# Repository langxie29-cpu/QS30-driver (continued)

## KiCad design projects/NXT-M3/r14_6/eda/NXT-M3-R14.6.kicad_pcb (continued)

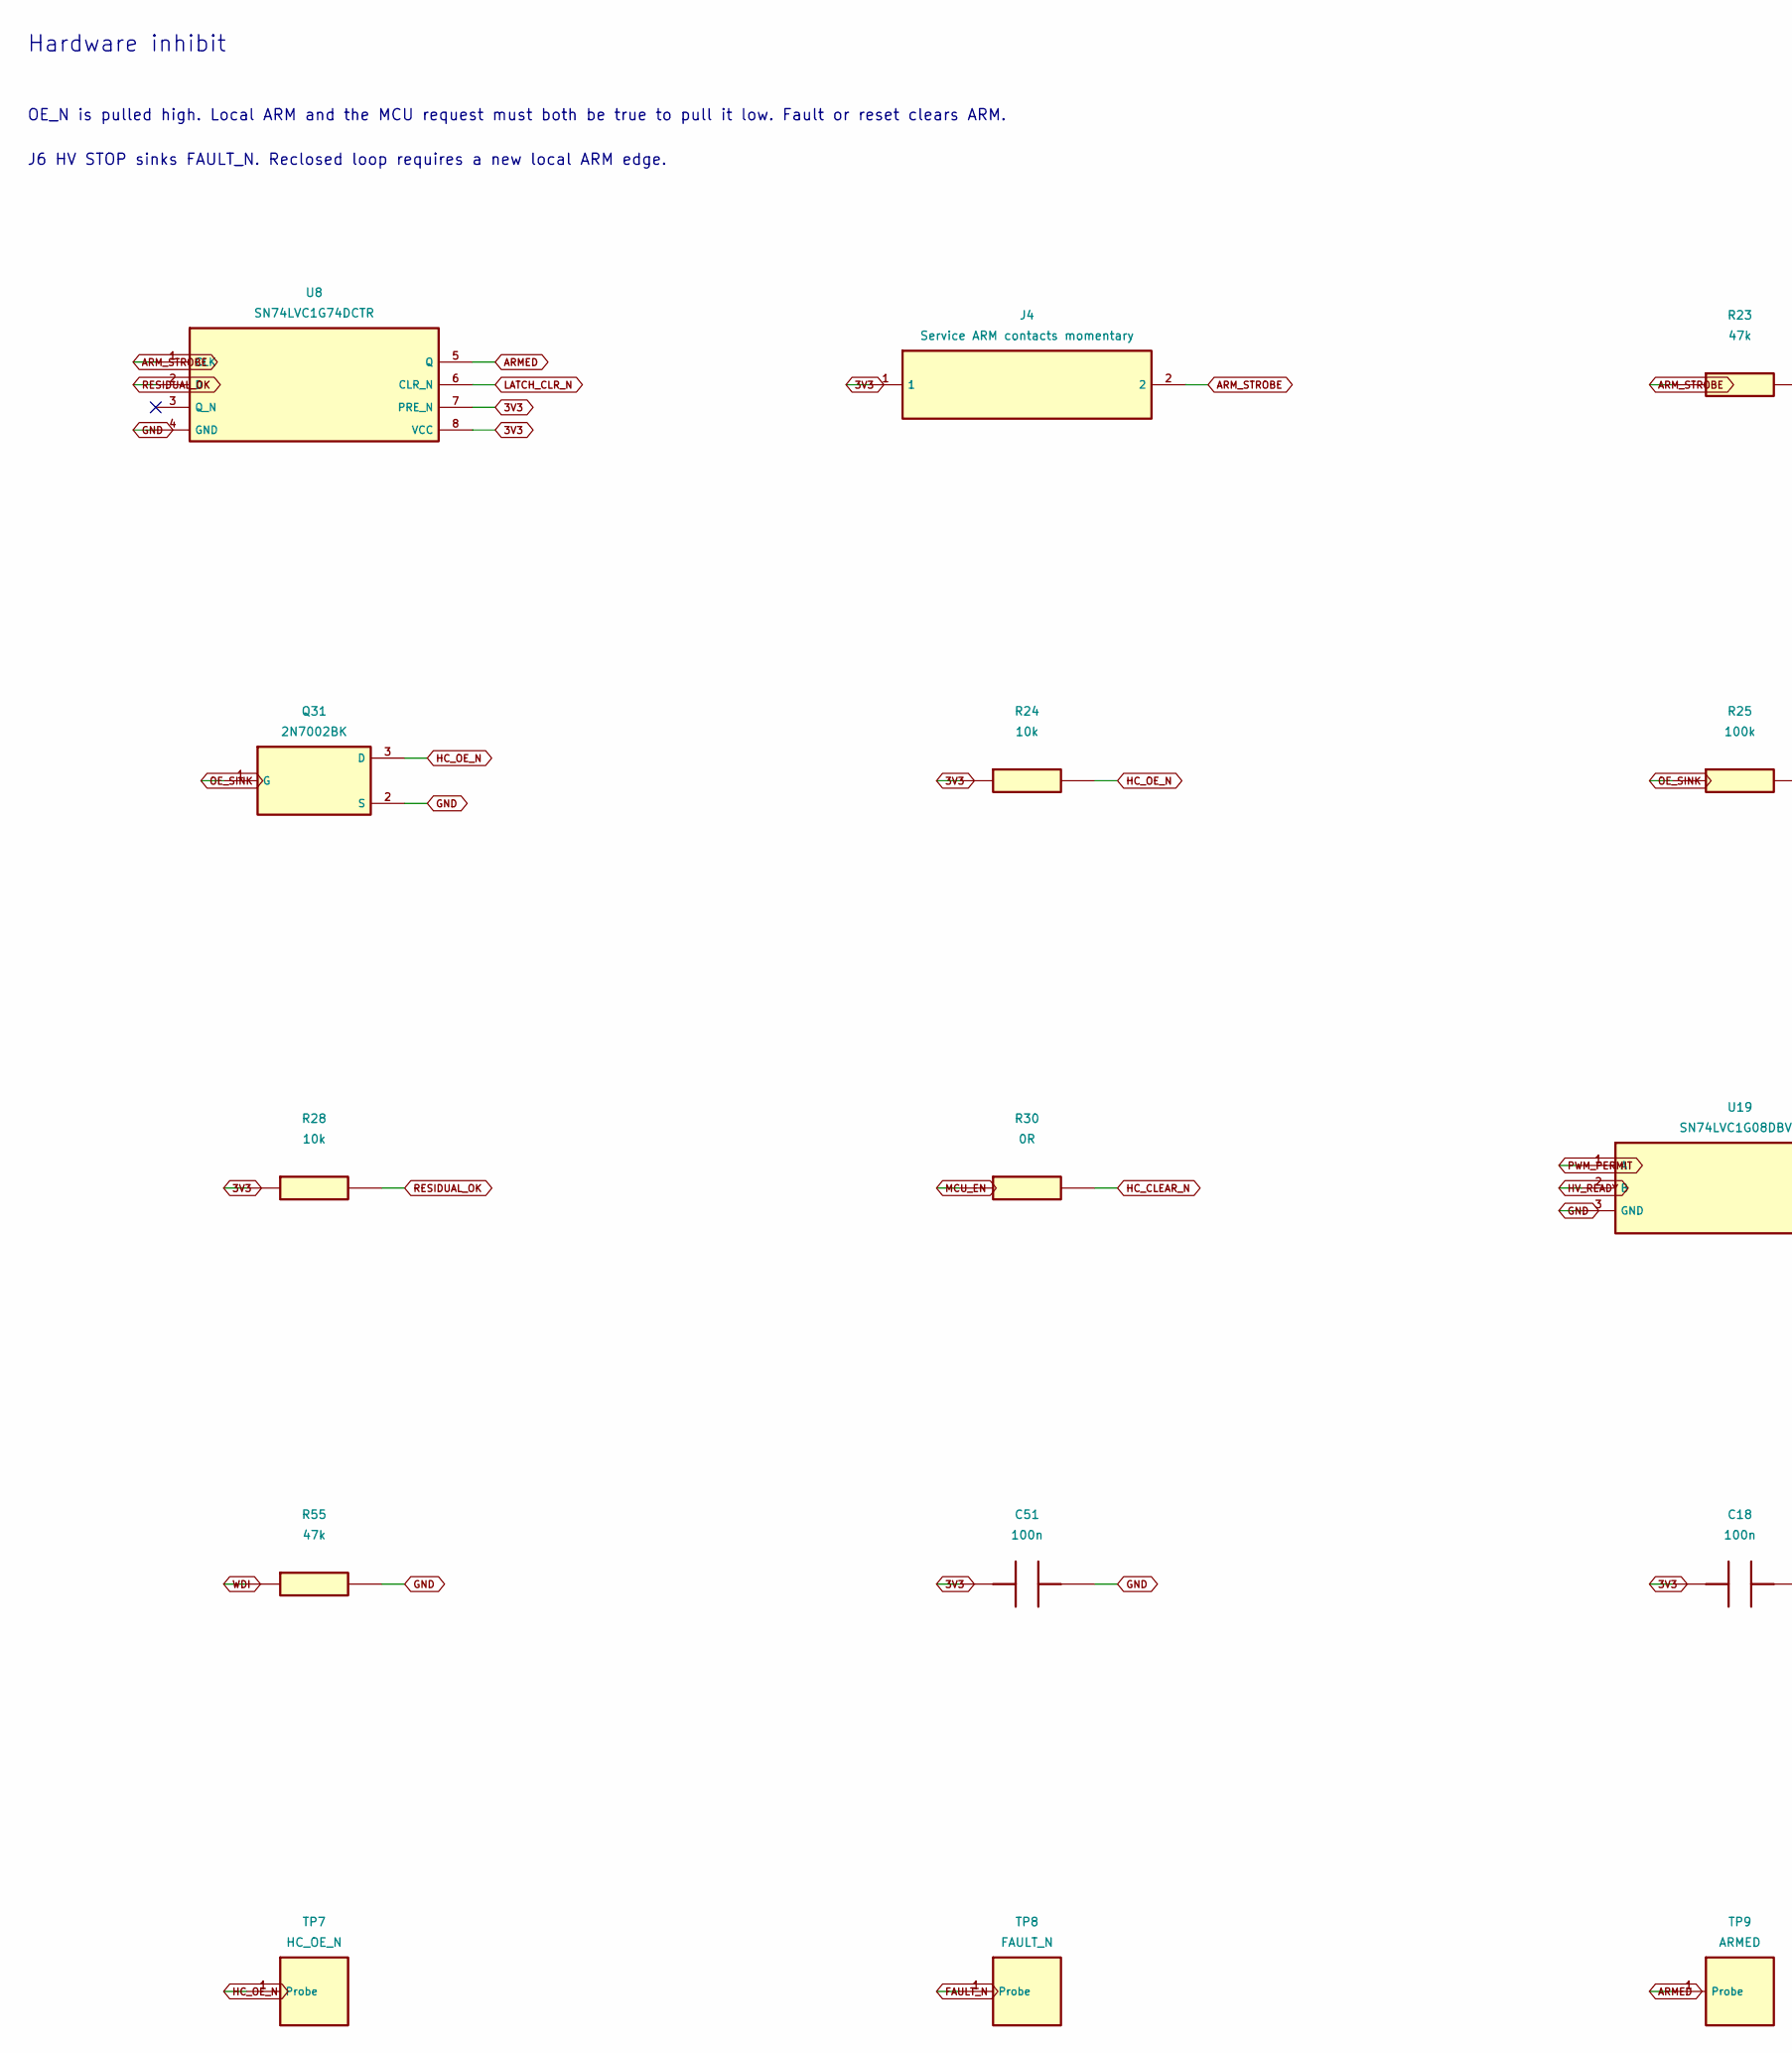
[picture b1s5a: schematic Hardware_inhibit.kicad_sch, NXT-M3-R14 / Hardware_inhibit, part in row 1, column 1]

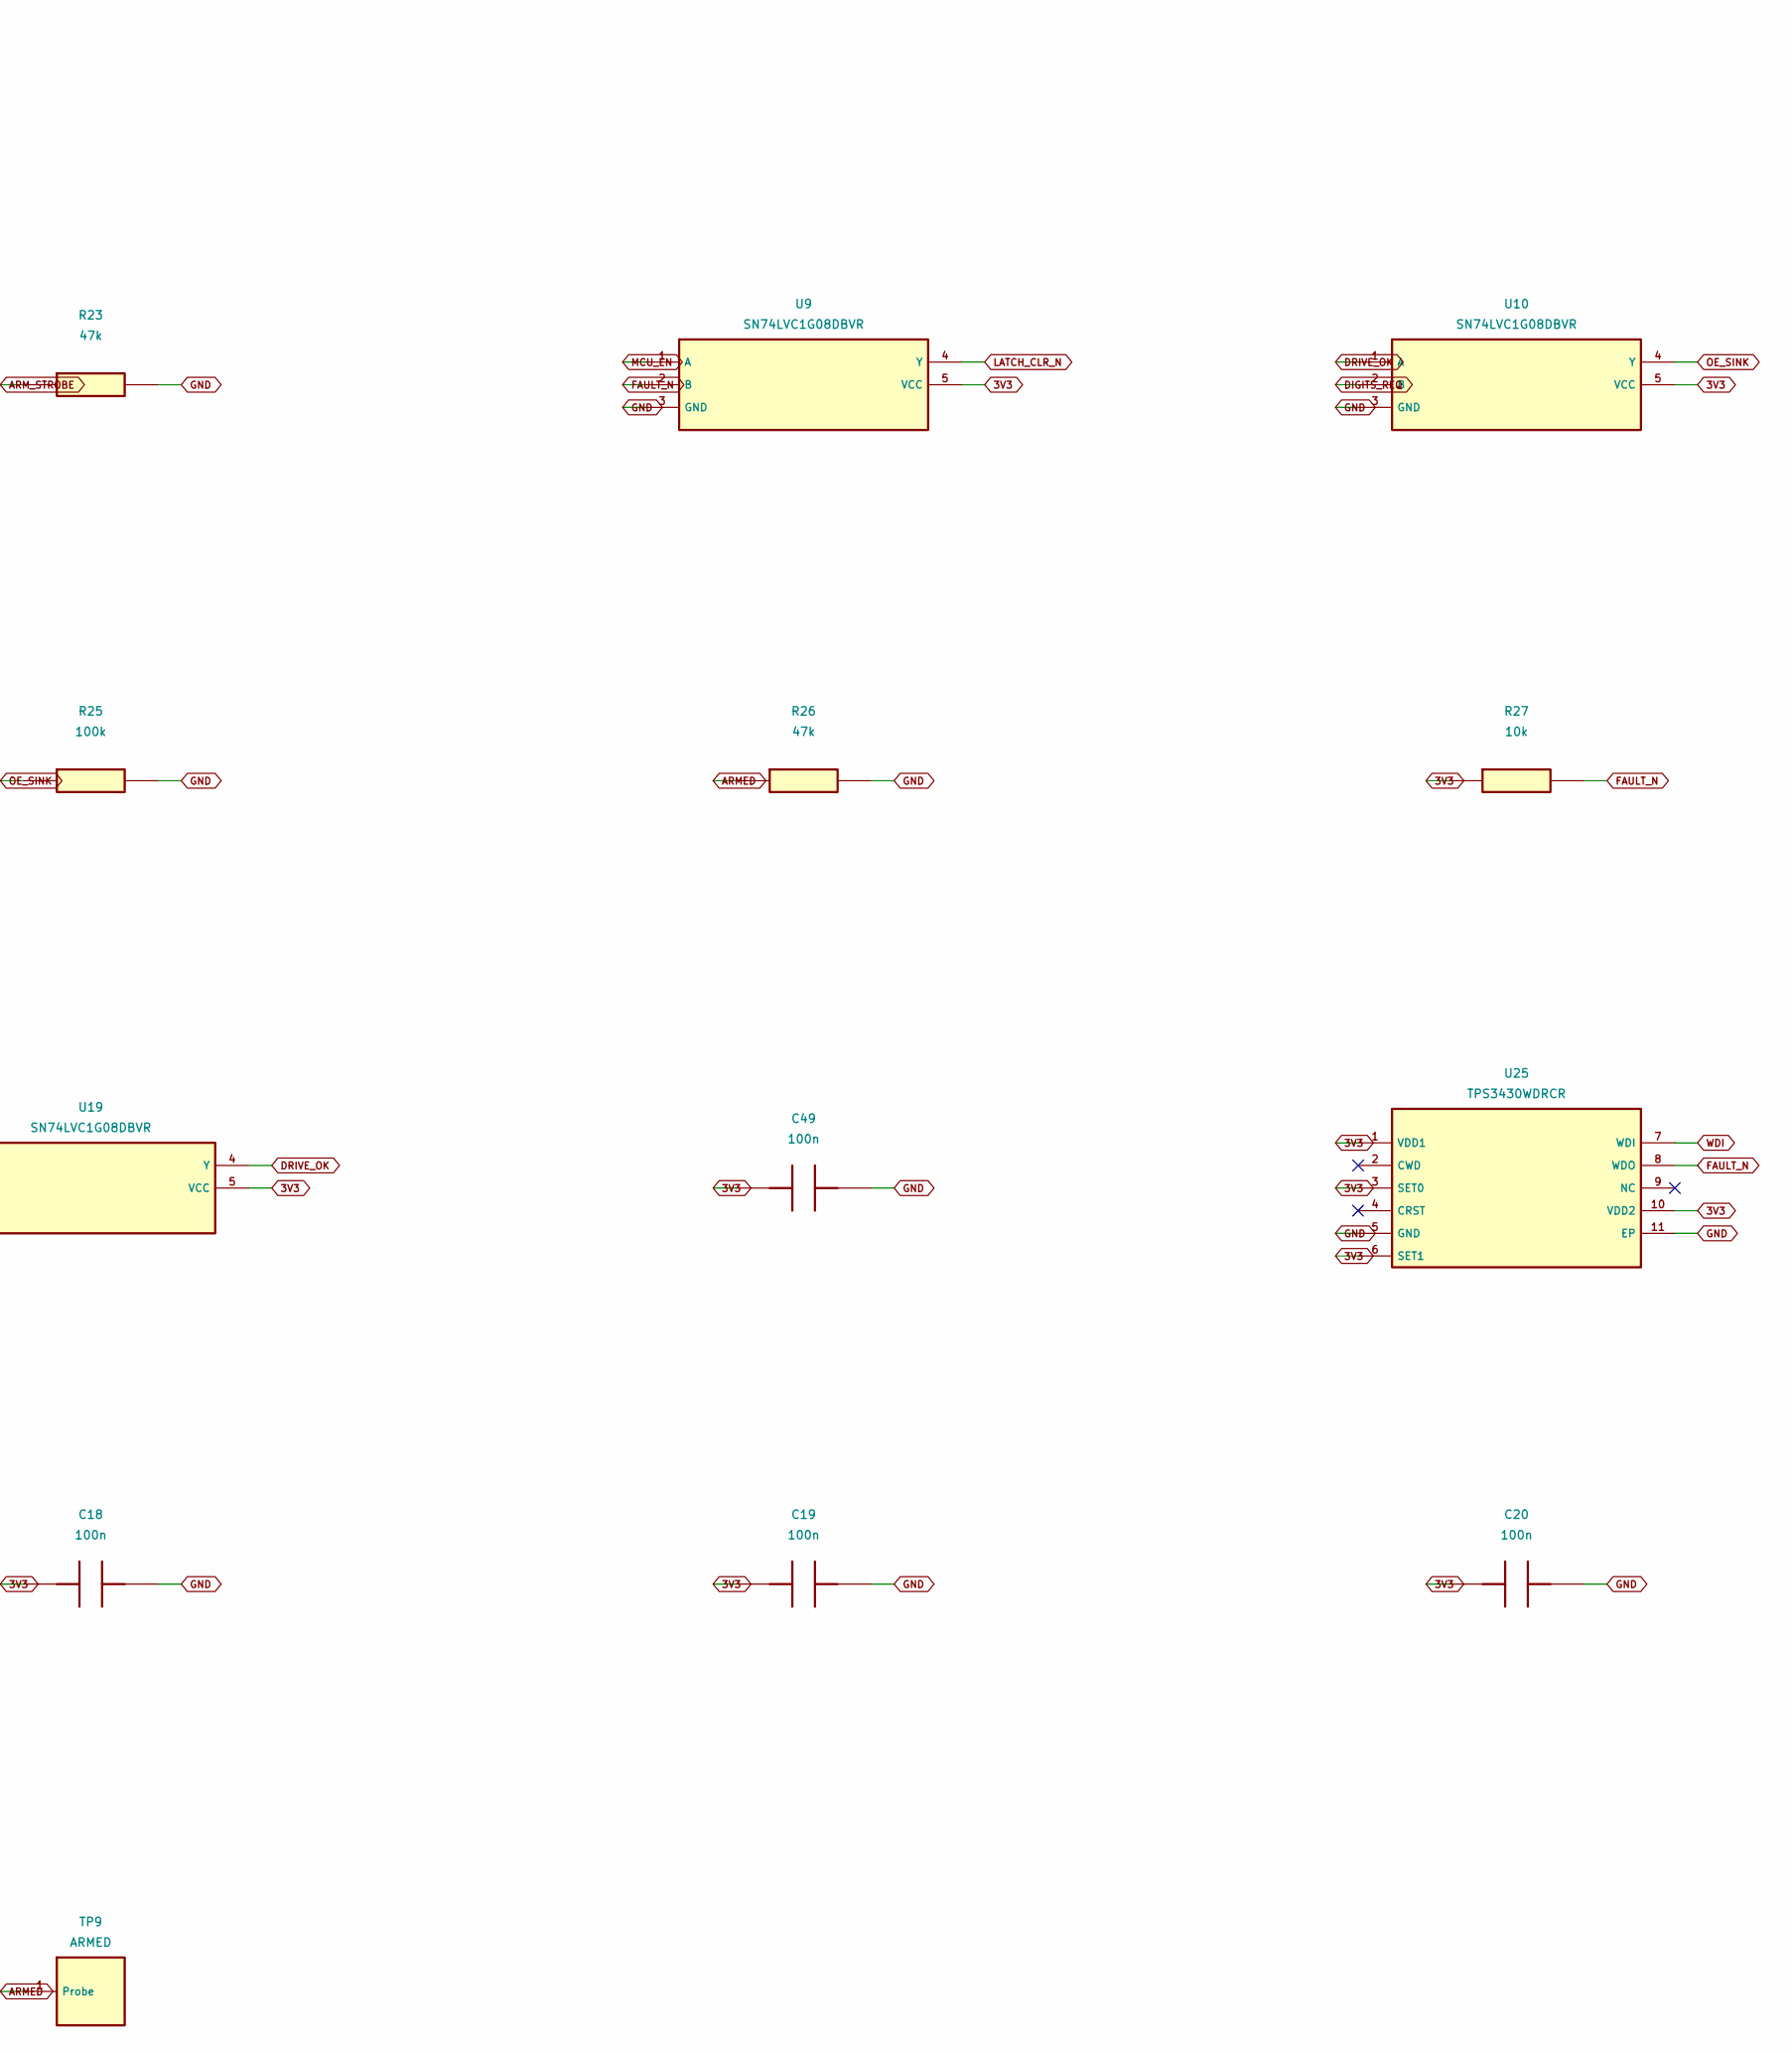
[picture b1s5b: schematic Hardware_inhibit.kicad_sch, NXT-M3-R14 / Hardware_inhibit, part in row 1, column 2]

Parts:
C18, C19, C20, C49, C51: 100n; C_0603_1608Metric
J4: Service ARM contacts momentary; PinHeader_1x02_P2.54mm_Vertical
Q31: 2N7002BK; SOT-23; MPN 2N7002BK,215
R23, R26, R55: 47k; R_0603_1608Metric
R24, R27, R28: 10k; R_0603_1608Metric
R25: 100k; R_0603_1608Metric
R30: 0R; R_0603_1608Metric
TP7: HC_OE_N; TestPoint_Pad_D1.5mm
TP8: FAULT_N; TestPoint_Pad_D1.5mm
TP9: ARMED; TestPoint_Pad_D1.5mm
U8: SN74LVC1G74DCTR; SSOP-8_2.95x2.8mm_P0.65mm; MPN SN74LVC1G74DCTR
U9, U10, U19: SN74LVC1G08DBVR; SOT-23-5; MPN SN74LVC1G08DBVR
U25: TPS3430WDRCR; Texas_DRC0010J; MPN TPS3430WDRCR

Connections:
3V3: C18.1, C19.1, C20.1, C49.1, C51.1, J4.1, R24.1, R27.1, R28.1, U8.7 (PRE_N), U8.8 (VCC), U9.5 (VCC), U10.5 (VCC), U19.5 (VCC), U25.1 (VDD1), U25.3 (SET0), U25.6 (SET1), U25.10 (VDD2); also elsewhere on the board
ARMED: R26.1, TP9.1, U8.5 (Q); also elsewhere on the board
ARM_STROBE: J4.2, R23.1, U8.1 (CLK)
DIGITS_REQ: U10.2 (B); also elsewhere on the board
DRIVE_OK: U10.1 (A), U19.4 (Y)
FAULT_N: R27.2, TP8.1, U9.2 (B), U25.8 (WDO); also elsewhere on the board
GND: C18.2, C19.2, C20.2, C49.2, C51.2, Q31.2 (S), R23.2, R25.2, R26.2, R55.2, U8.4 (GND), U9.3 (GND), U10.3 (GND), U19.3 (GND), U25.5 (GND), U25.11 (EP); also elsewhere on the board
HC_CLEAR_N: R30.2; also elsewhere on the board
HC_OE_N: Q31.3 (D), R24.2, TP7.1; also elsewhere on the board
HV_READY: U19.2 (B); also elsewhere on the board
LATCH_CLR_N: U8.6 (CLR_N), U9.4 (Y)
MCU_EN: R30.1, U9.1 (A); also elsewhere on the board
OE_SINK: Q31.1 (G), R25.1, U10.4 (Y)
PWM_PERMIT: U19.1 (A); also elsewhere on the board
RESIDUAL_OK: R28.2, U8.2 (D); also elsewhere on the board
WDI: R55.1, U25.7 (WDI); also elsewhere on the board

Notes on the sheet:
Hardware inhibit
OE_N is pulled high. Local ARM and the MCU request must both be true to pull it low. Fault or reset clears ARM.
J6 HV STOP sinks FAULT_N. Reclosed loop requires a new local ARM edge.

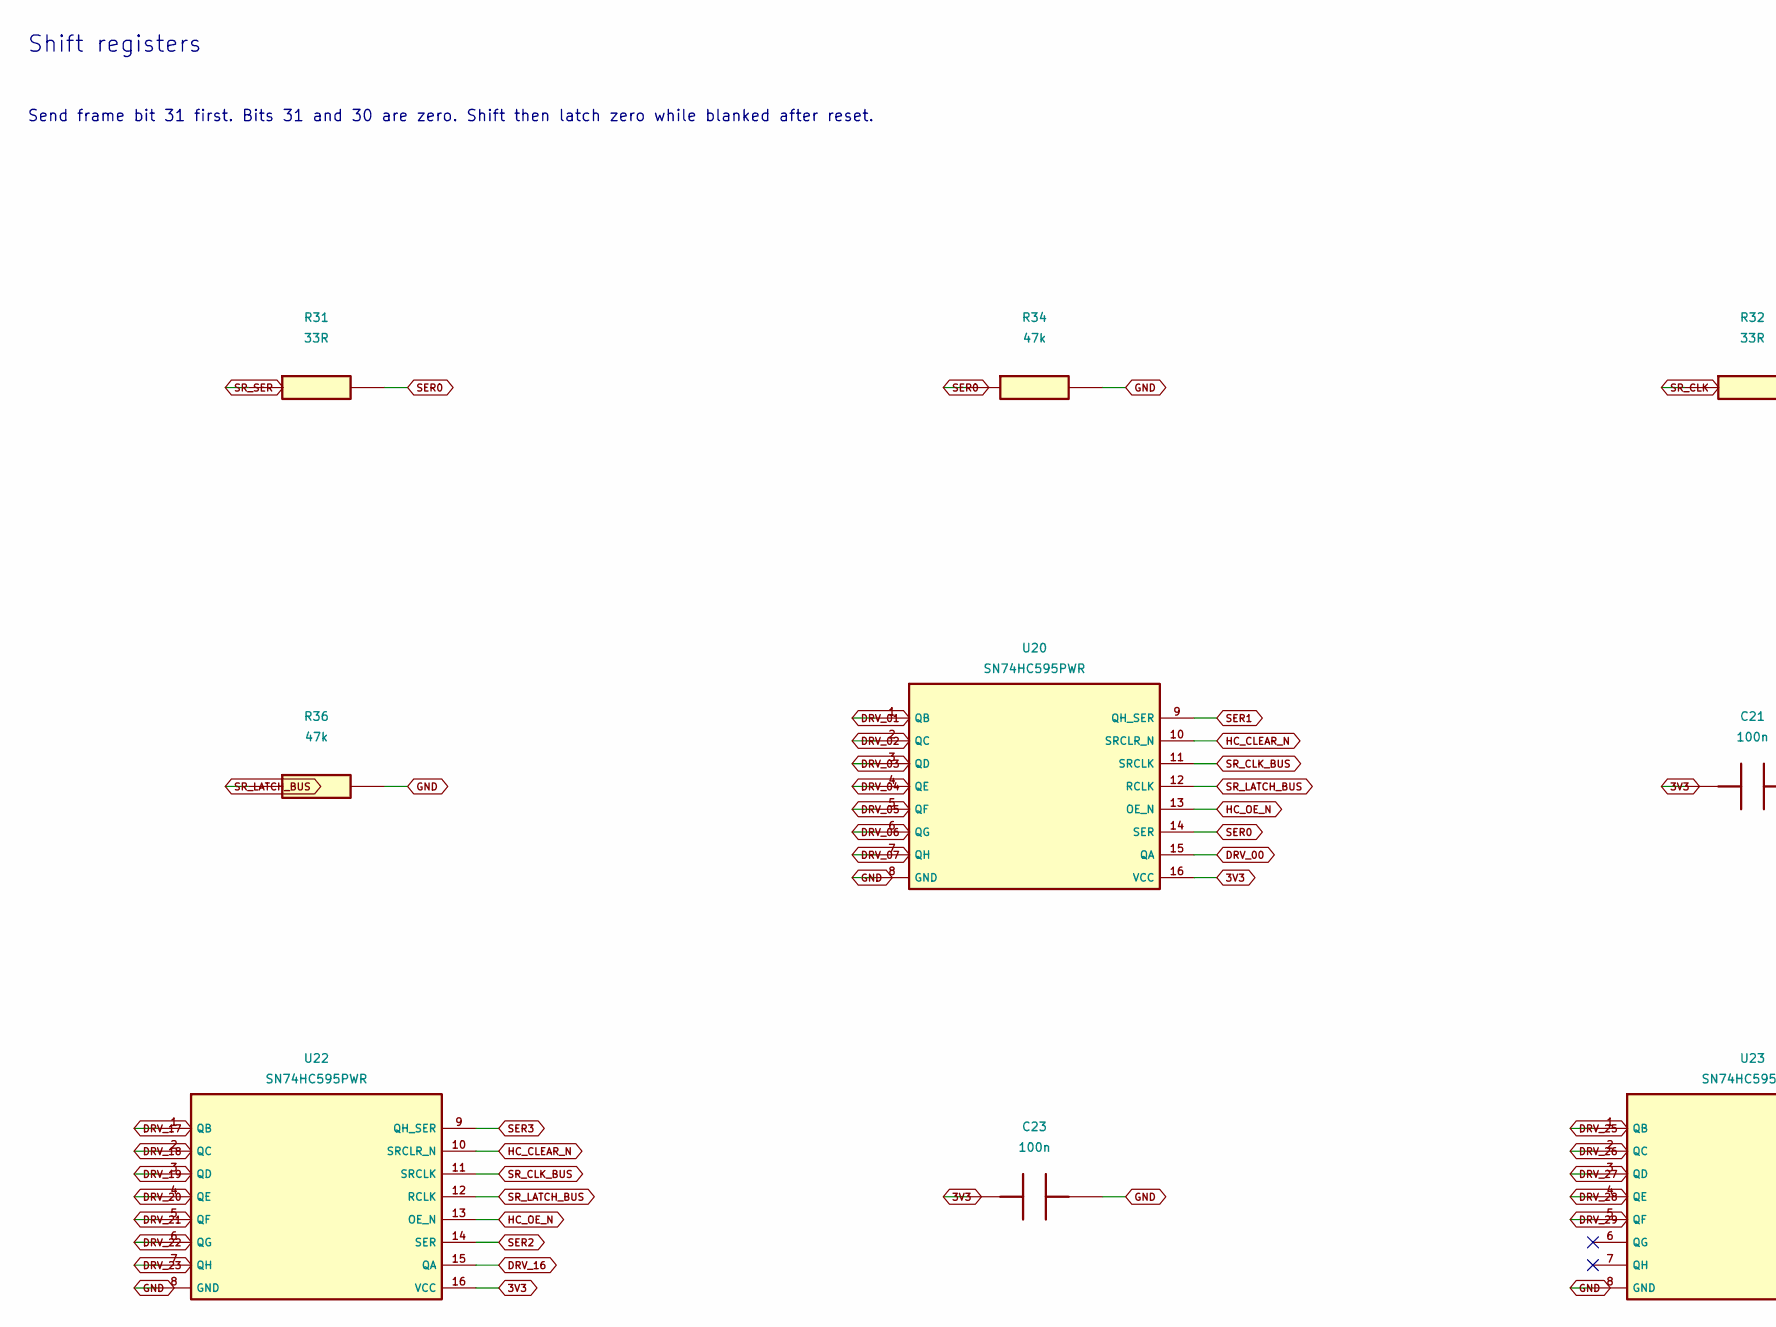
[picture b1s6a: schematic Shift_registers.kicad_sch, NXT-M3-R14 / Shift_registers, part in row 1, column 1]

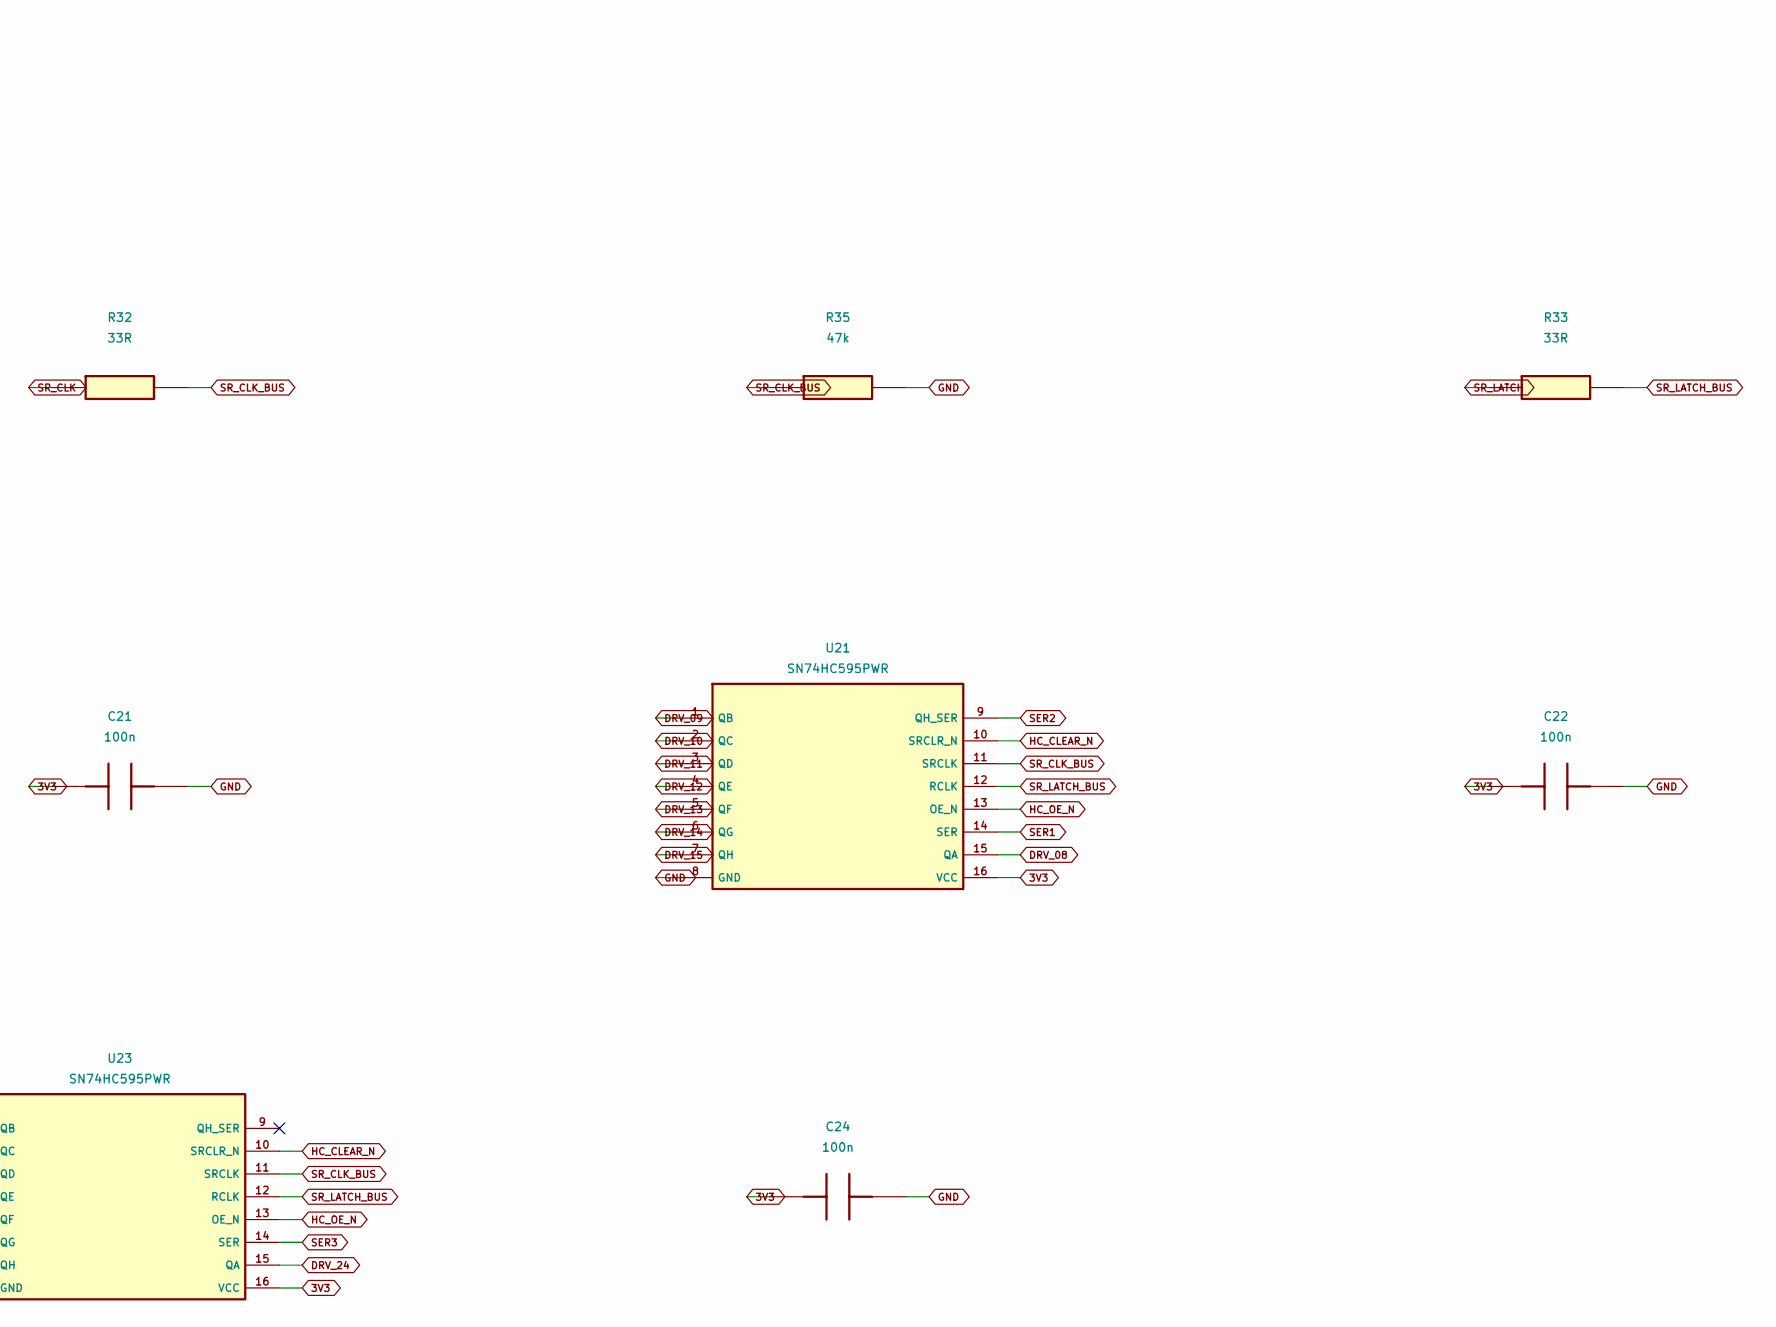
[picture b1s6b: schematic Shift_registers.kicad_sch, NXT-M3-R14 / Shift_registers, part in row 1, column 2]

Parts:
C21, C22, C23, C24: 100n; C_0603_1608Metric
R31, R32, R33: 33R; R_0603_1608Metric
R34, R35, R36: 47k; R_0603_1608Metric
U20, U21, U22, U23: SN74HC595PWR; TSSOP-16_4.4x5mm_P0.65mm; MPN SN74HC595PWR

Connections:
3V3: C21.1, C22.1, C23.1, C24.1, U20.16 (VCC), U21.16 (VCC), U22.16 (VCC), U23.16 (VCC); also elsewhere on the board
DRV_00: U20.15 (QA); also elsewhere on the board
DRV_01: U20.1 (QB); also elsewhere on the board
DRV_02: U20.2 (QC); also elsewhere on the board
DRV_03: U20.3 (QD); also elsewhere on the board
DRV_04: U20.4 (QE); also elsewhere on the board
DRV_05: U20.5 (QF); also elsewhere on the board
DRV_06: U20.6 (QG); also elsewhere on the board
DRV_07: U20.7 (QH); also elsewhere on the board
DRV_08: U21.15 (QA); also elsewhere on the board
DRV_09: U21.1 (QB); also elsewhere on the board
DRV_10: U21.2 (QC); also elsewhere on the board
DRV_11: U21.3 (QD); also elsewhere on the board
DRV_12: U21.4 (QE); also elsewhere on the board
DRV_13: U21.5 (QF); also elsewhere on the board
DRV_14: U21.6 (QG); also elsewhere on the board
DRV_15: U21.7 (QH); also elsewhere on the board
DRV_16: U22.15 (QA); also elsewhere on the board
DRV_17: U22.1 (QB); also elsewhere on the board
DRV_18: U22.2 (QC); also elsewhere on the board
DRV_19: U22.3 (QD); also elsewhere on the board
DRV_20: U22.4 (QE); also elsewhere on the board
DRV_21: U22.5 (QF); also elsewhere on the board
DRV_22: U22.6 (QG); also elsewhere on the board
DRV_23: U22.7 (QH); also elsewhere on the board
DRV_24: U23.15 (QA); also elsewhere on the board
DRV_25: U23.1 (QB); also elsewhere on the board
DRV_26: U23.2 (QC); also elsewhere on the board
DRV_27: U23.3 (QD); also elsewhere on the board
DRV_28: U23.4 (QE); also elsewhere on the board
DRV_29: U23.5 (QF); also elsewhere on the board
GND: C21.2, C22.2, C23.2, C24.2, R34.2, R35.2, R36.2, U20.8 (GND), U21.8 (GND), U22.8 (GND), U23.8 (GND); also elsewhere on the board
HC_CLEAR_N: U20.10 (SRCLR_N), U21.10 (SRCLR_N), U22.10 (SRCLR_N), U23.10 (SRCLR_N); also elsewhere on the board
HC_OE_N: U20.13 (OE_N), U21.13 (OE_N), U22.13 (OE_N), U23.13 (OE_N); also elsewhere on the board
SER0: R31.2, R34.1, U20.14 (SER)
SER1: U20.9 (QH_SER), U21.14 (SER)
SER2: U21.9 (QH_SER), U22.14 (SER)
SER3: U22.9 (QH_SER), U23.14 (SER)
SR_CLK: R32.1; also elsewhere on the board
SR_CLK_BUS: R32.2, R35.1, U20.11 (SRCLK), U21.11 (SRCLK), U22.11 (SRCLK), U23.11 (SRCLK)
SR_LATCH: R33.1; also elsewhere on the board
SR_LATCH_BUS: R33.2, R36.1, U20.12 (RCLK), U21.12 (RCLK), U22.12 (RCLK), U23.12 (RCLK)
SR_SER: R31.1; also elsewhere on the board

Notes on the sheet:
Shift registers
Send frame bit 31 first. Bits 31 and 30 are zero. Shift then latch zero while blanked after reset.

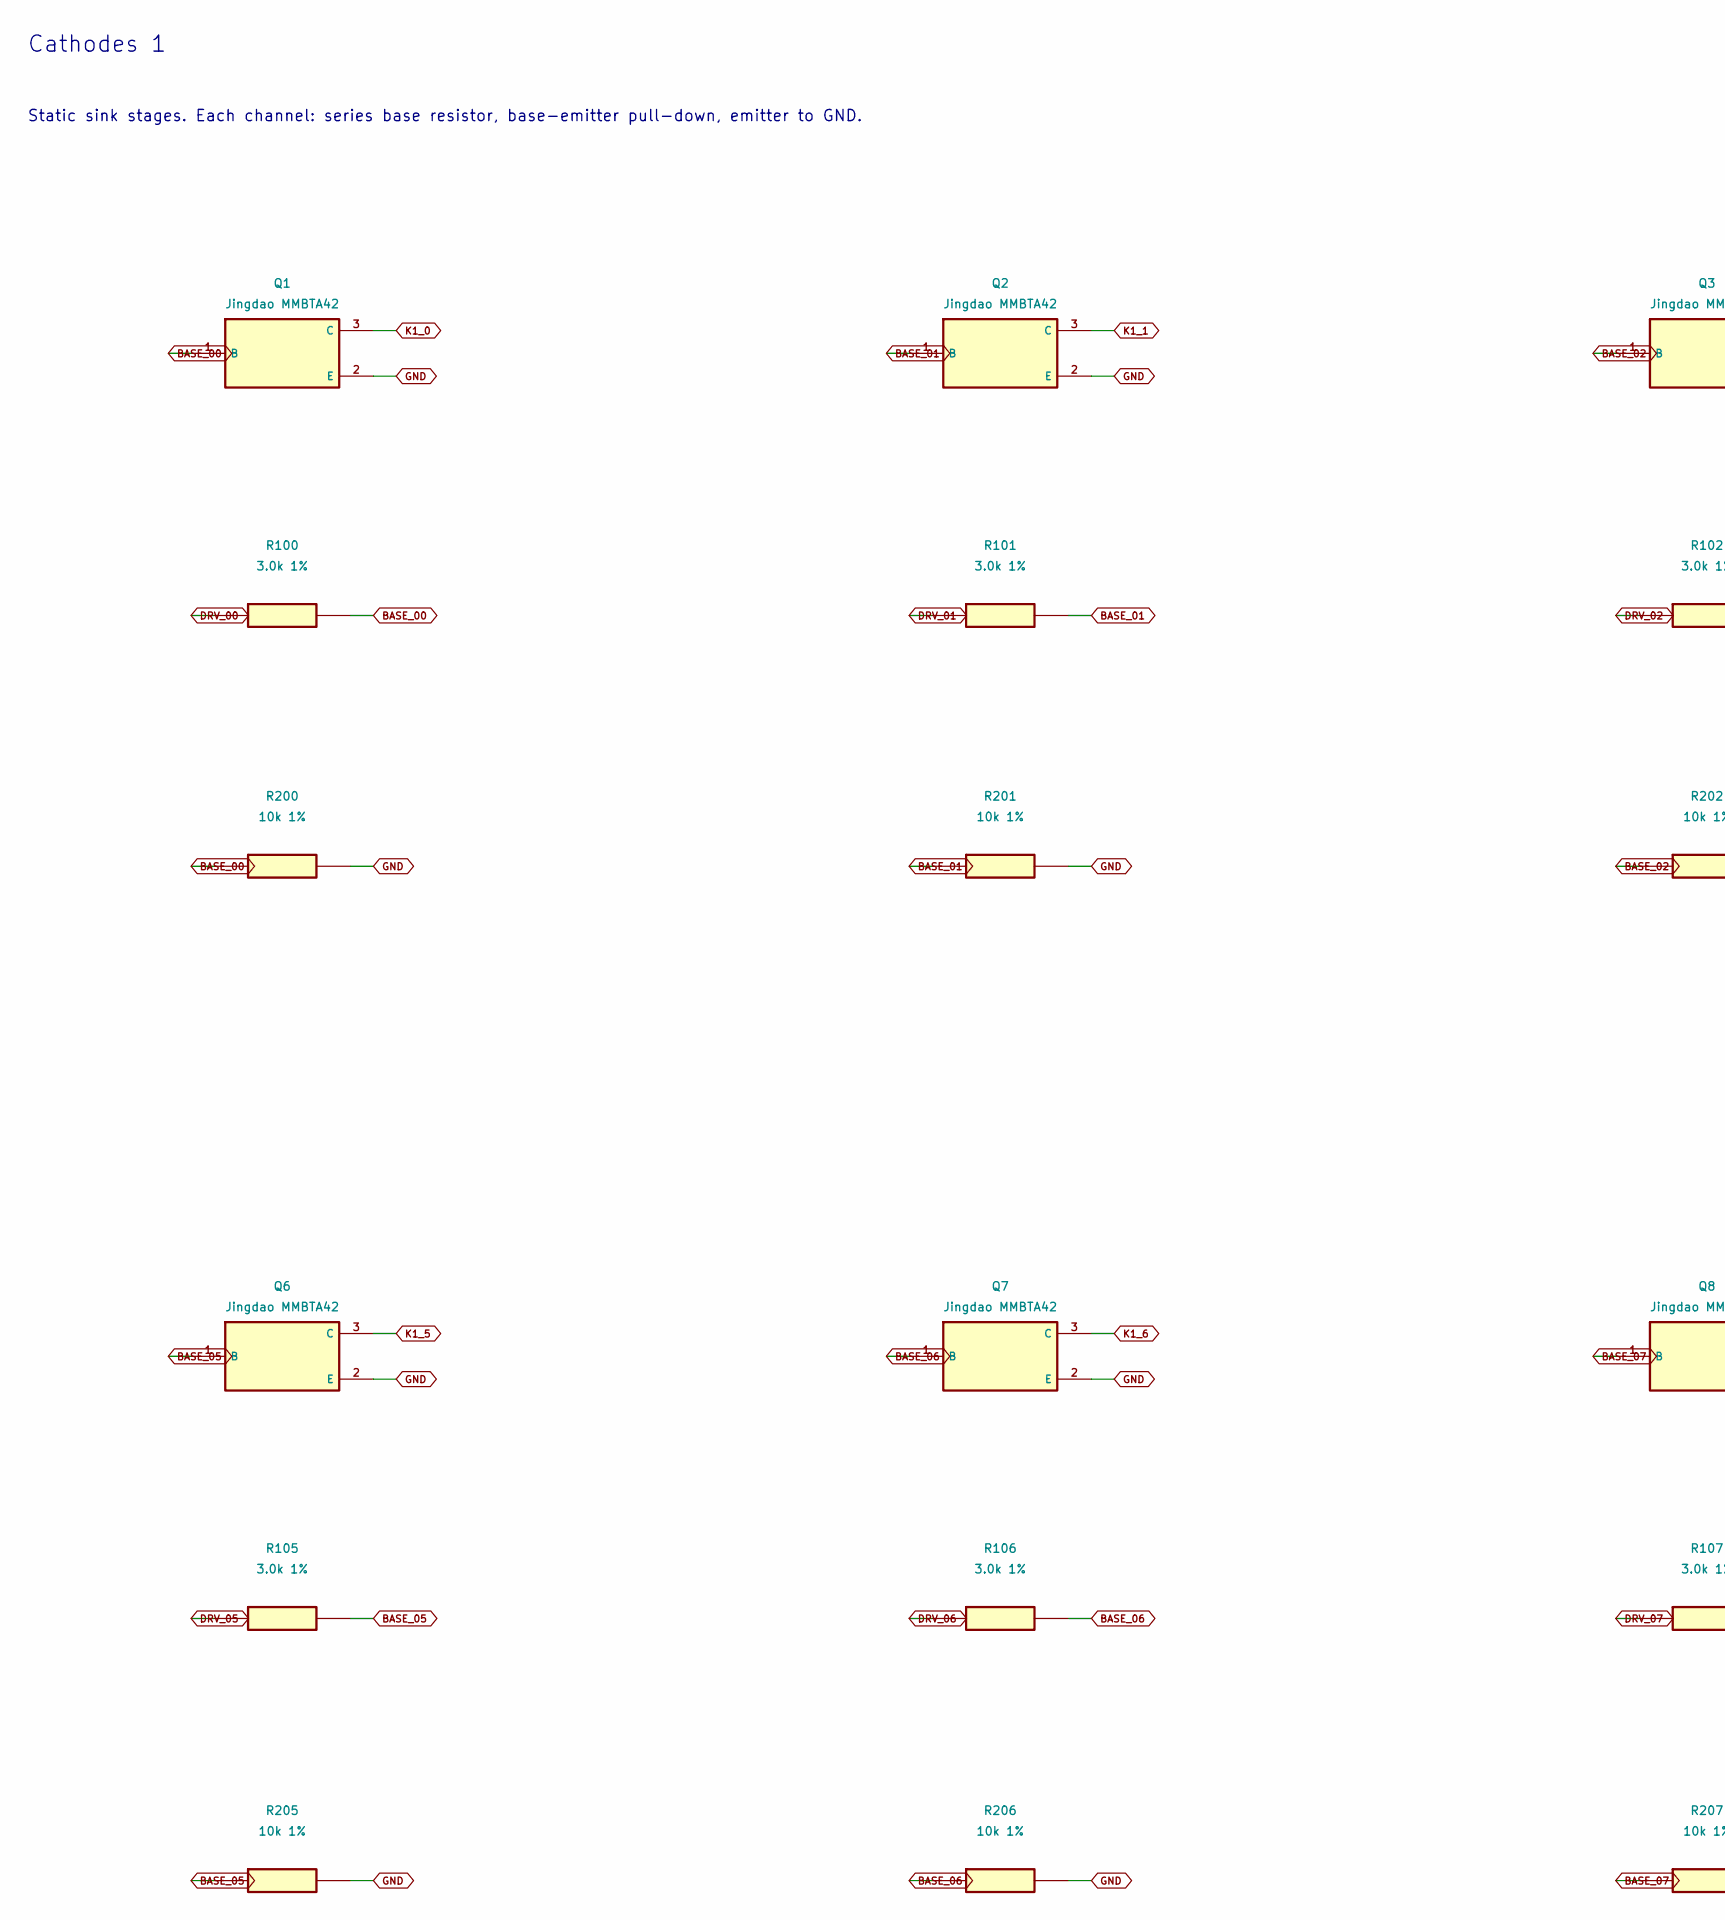
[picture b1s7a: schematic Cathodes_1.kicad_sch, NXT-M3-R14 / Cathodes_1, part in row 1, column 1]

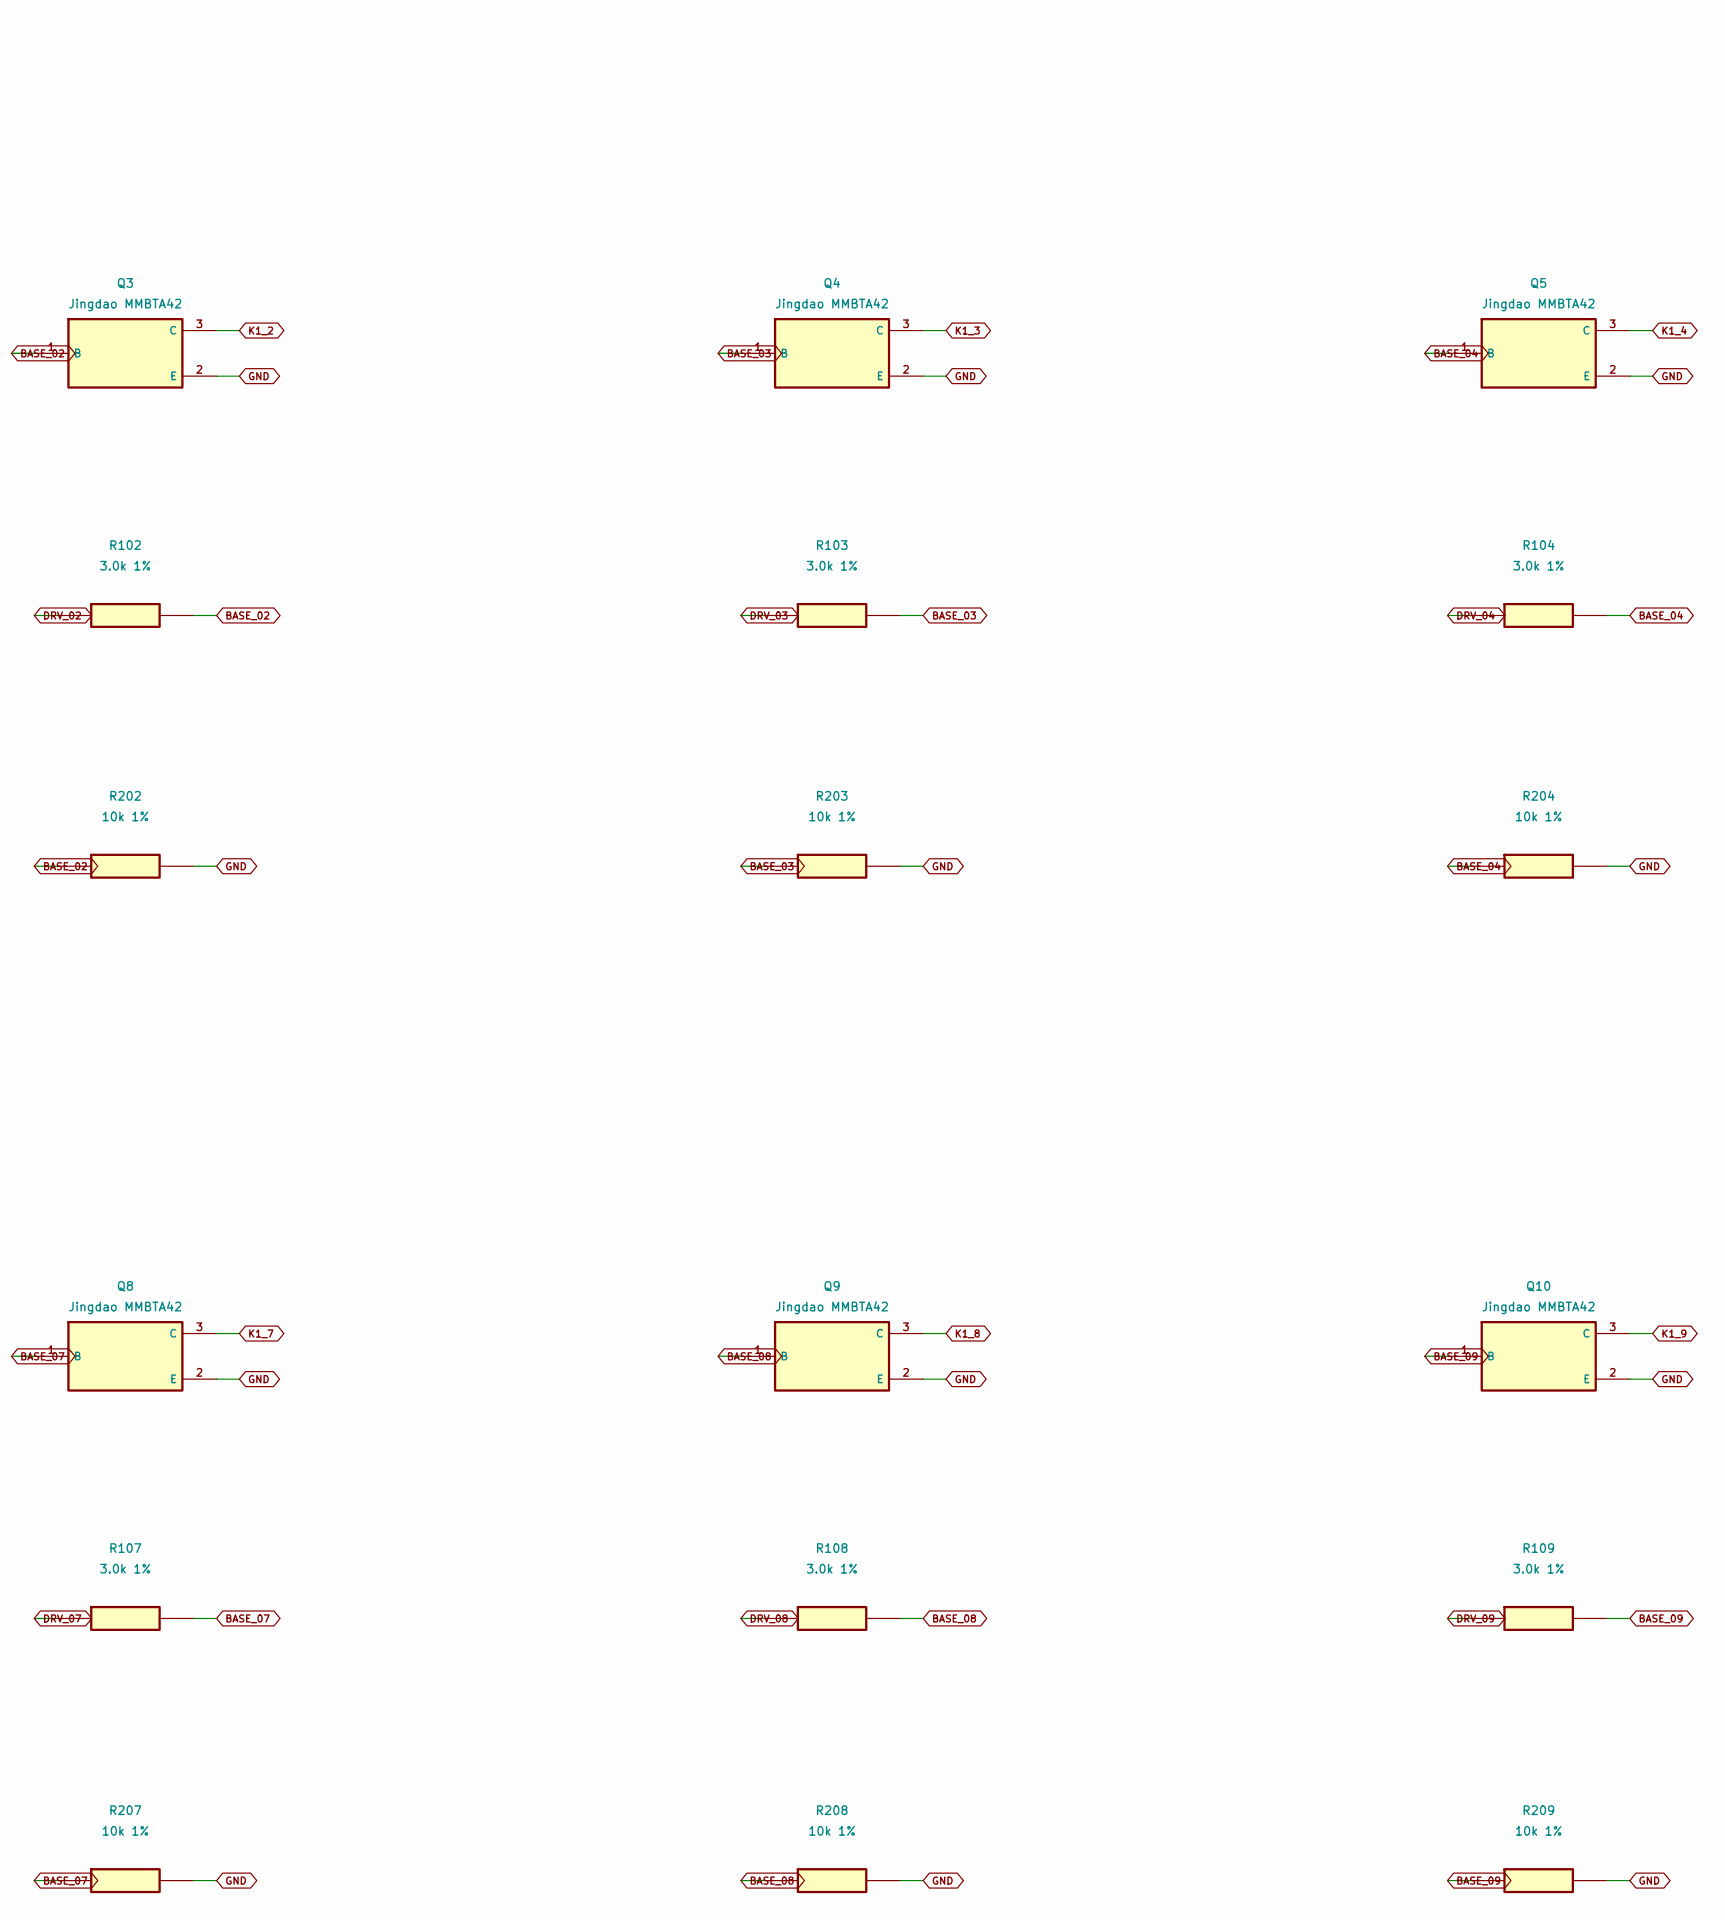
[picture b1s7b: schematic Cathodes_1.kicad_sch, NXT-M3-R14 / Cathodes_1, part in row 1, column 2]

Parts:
Q1, Q2, Q3, Q4, Q5, Q6, Q7, Q8, Q9, Q10: Jingdao MMBTA42; Jingdao_MMBTA42_nominal; MPN MMBTA42 / C4749118
R100, R101, R102, R103, R104, R105, R106, R107, R108, R109: 3.0k 1%; R_0603_1608Metric; MPN RC0603FR-073KL
R200, R201, R202, R203, R204, R205, R206, R207, R208, R209: 10k 1%; R_0603_1608Metric; MPN RC0603FR-0710KL

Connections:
BASE_00: Q1.1 (B), R100.2, R200.1
BASE_01: Q2.1 (B), R101.2, R201.1
BASE_02: Q3.1 (B), R102.2, R202.1
BASE_03: Q4.1 (B), R103.2, R203.1
BASE_04: Q5.1 (B), R104.2, R204.1
BASE_05: Q6.1 (B), R105.2, R205.1
BASE_06: Q7.1 (B), R106.2, R206.1
BASE_07: Q8.1 (B), R107.2, R207.1
BASE_08: Q9.1 (B), R108.2, R208.1
BASE_09: Q10.1 (B), R109.2, R209.1
DRV_00: R100.1; also elsewhere on the board
DRV_01: R101.1; also elsewhere on the board
DRV_02: R102.1; also elsewhere on the board
DRV_03: R103.1; also elsewhere on the board
DRV_04: R104.1; also elsewhere on the board
DRV_05: R105.1; also elsewhere on the board
DRV_06: R106.1; also elsewhere on the board
DRV_07: R107.1; also elsewhere on the board
DRV_08: R108.1; also elsewhere on the board
DRV_09: R109.1; also elsewhere on the board
GND: Q1.2 (E), Q2.2 (E), Q3.2 (E), Q4.2 (E), Q5.2 (E), Q6.2 (E), Q7.2 (E), Q8.2 (E), Q9.2 (E), Q10.2 (E), R200.2, R201.2, R202.2, R203.2, R204.2, R205.2, R206.2, R207.2, R208.2, R209.2; also elsewhere on the board
K1_0: Q1.3 (C); also elsewhere on the board
K1_1: Q2.3 (C); also elsewhere on the board
K1_2: Q3.3 (C); also elsewhere on the board
K1_3: Q4.3 (C); also elsewhere on the board
K1_4: Q5.3 (C); also elsewhere on the board
K1_5: Q6.3 (C); also elsewhere on the board
K1_6: Q7.3 (C); also elsewhere on the board
K1_7: Q8.3 (C); also elsewhere on the board
K1_8: Q9.3 (C); also elsewhere on the board
K1_9: Q10.3 (C); also elsewhere on the board

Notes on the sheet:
Cathodes 1
Static sink stages. Each channel: series base resistor, base-emitter pull-down, emitter to GND.
